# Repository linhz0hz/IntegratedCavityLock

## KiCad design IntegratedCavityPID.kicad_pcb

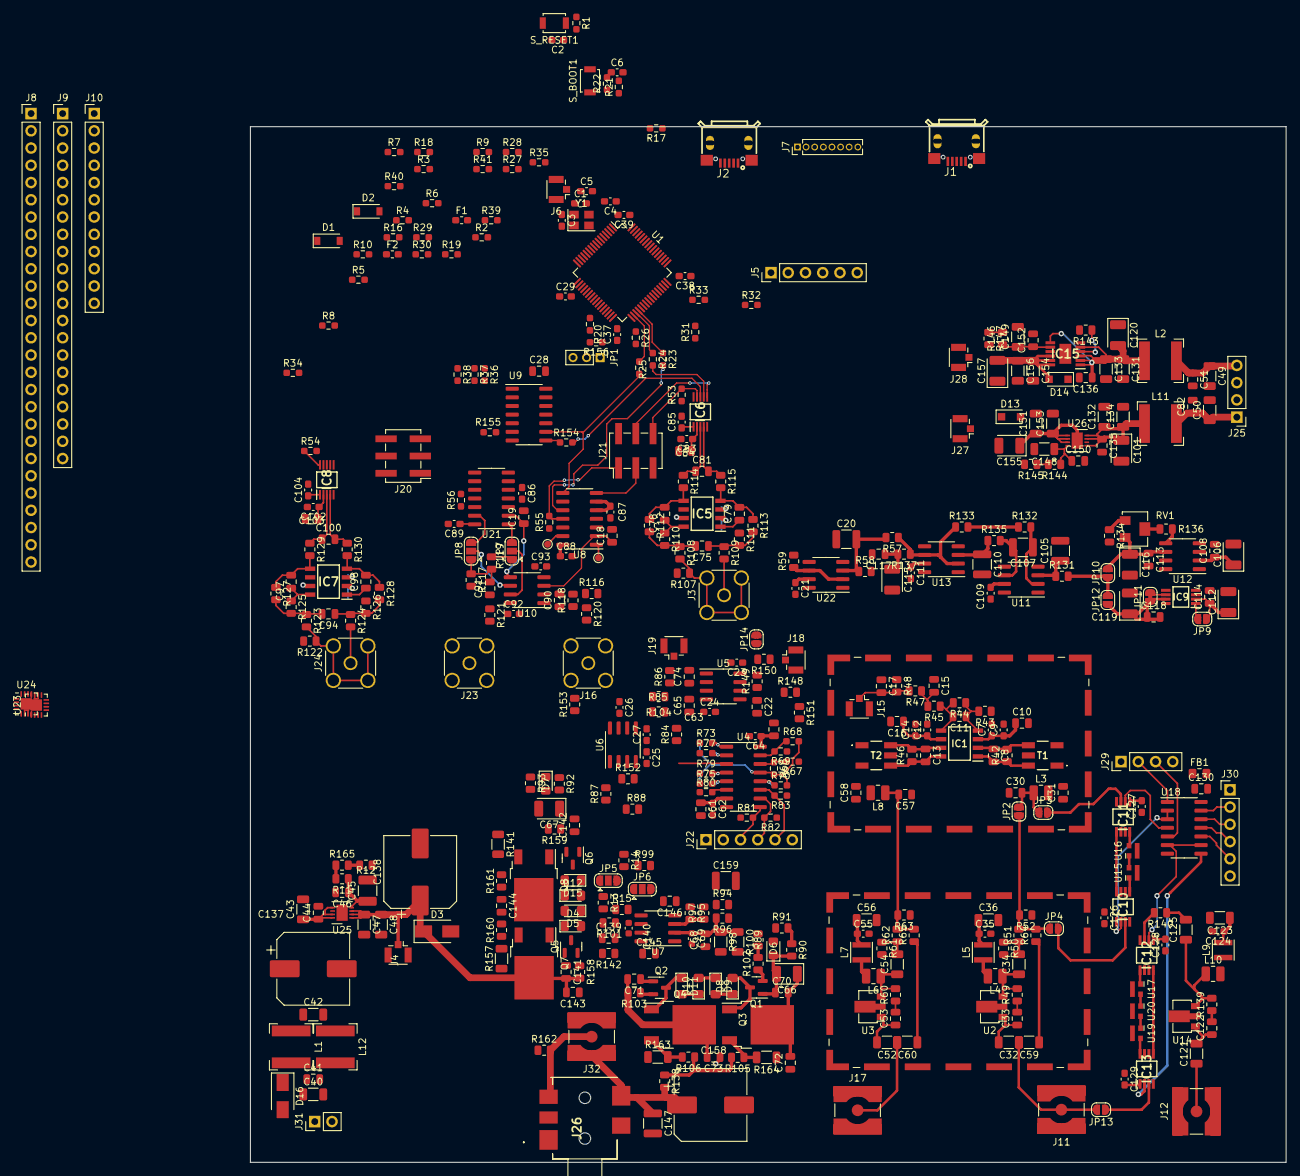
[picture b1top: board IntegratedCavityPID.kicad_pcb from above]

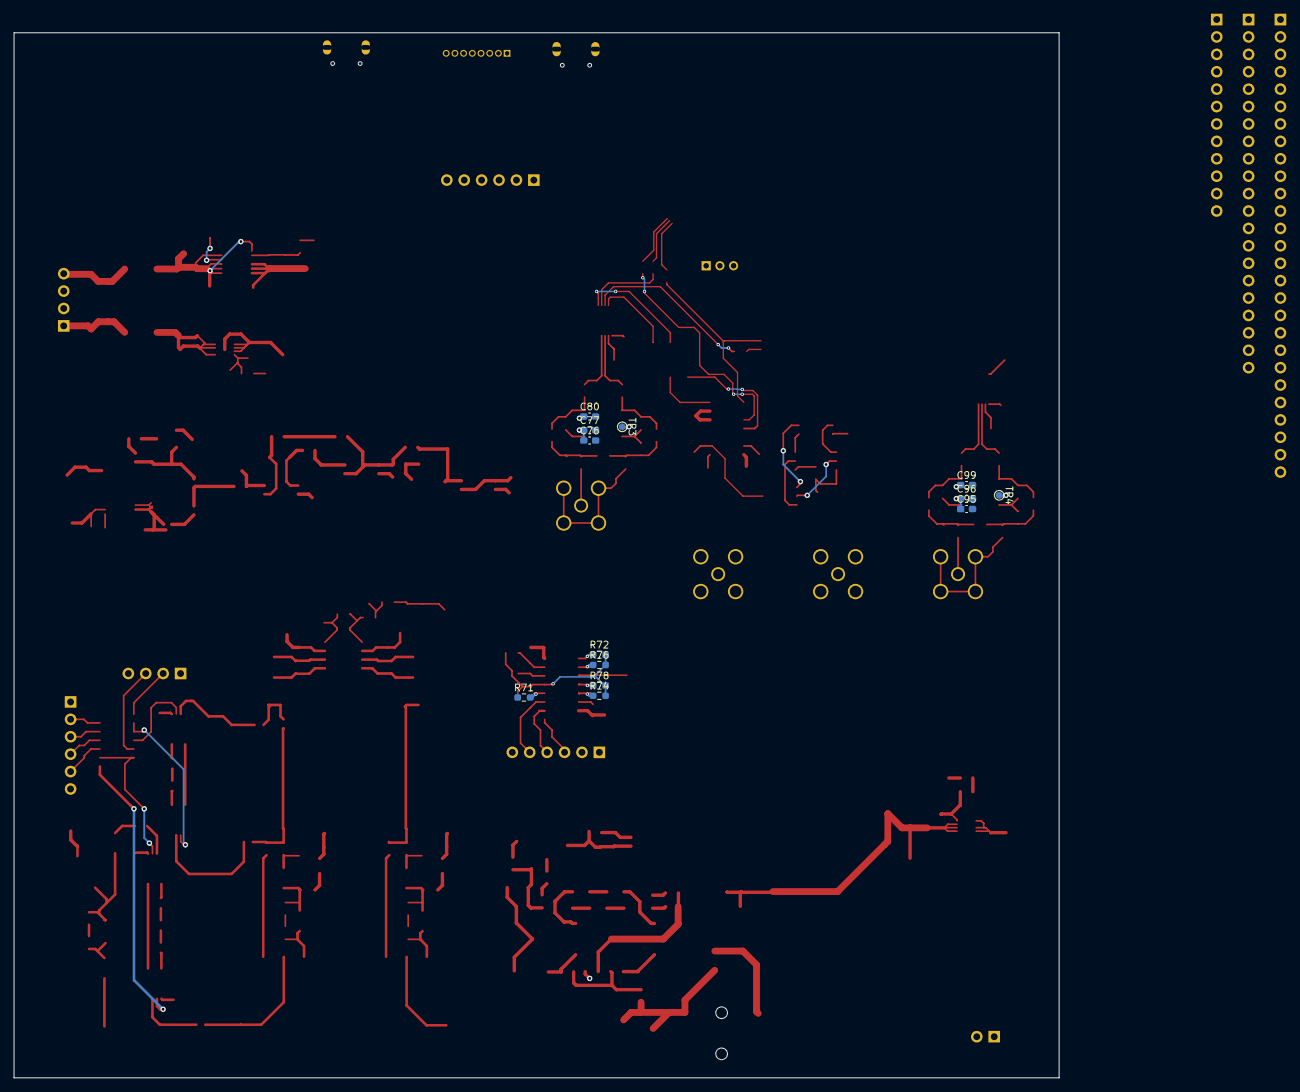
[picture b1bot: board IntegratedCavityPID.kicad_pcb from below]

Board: 4 copper layers, 152.5 x 152.5 mm, 456 parts (13 on the bottom side), 306 nets.

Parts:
C1, C3, C4, C5: 10p; C_0603_1608Metric_Pad1.08x0.95mm_HandSolder
C2, C6, C29, C37, C38, C39: X7R 0.1u; C_0603_1608Metric_Pad1.08x0.95mm_HandSolder
C7, C12: 10n; C_0603_1608Metric_Pad1.08x0.95mm_HandSolder
C8, C13: 22p; C_0805_2012Metric
C9, C14, C21, C23, C24, C25, C26, C27, C62, C64, C80, C83, C85, C86, C87, C88, C89, C92, C93, C99, C102, C104, C109, C111, C126, C127, C128, C129: 0.1uF; C_0603_1608Metric_Pad1.08x0.95mm_HandSolder
C10, C16, C61, C63, C84, C103: 1uF; C_0805_2012Metric
C11: 100p; C_0805_2012Metric
C15, C17: 4.7n; C_0805_2012Metric
C18, C19, C22, C65, C74, C117: dnp; C_0805_2012Metric
C20, C105, C107, C110, C147, C159: ECPU1C105MA5; C_1210_3225Metric
C28, C41, C44, C46, C51, C70, C71, C72, C73, C82, C130, C135, C136, C141, C142, C143, C144, C145, C146, C150, C152: 0.1uF; C_0805_2012Metric
C30, C31, C57, C58: 150p; C_0805_2012Metric
C32, C34, C36, C52, C54, C56, C59, C60, C121, C123, C125: 1u; C_1206_3216Metric
C33, C53, C108, C113, C114, C118, C122: 0.1u; C_0805_2012Metric
C35, C55, C124: 0.1u; C_0603_1608Metric_Pad1.08x0.95mm_HandSolder
C40, C42, C48: 2.2uF; C_1206_3216Metric
C43, C47, C133, C134, C151, C154: 1uF; C_1206_3216Metric
C45: dnp; C_1210_3225Metric_Pad1.33x2.70mm_HandSolder
C49, C50, C131, C132, C153, C156: 4.7uF; C_1206_3216Metric
C66, C67, C115: TAJA106K016RNJ; CP_EIA-3528-12_Kemet-T
C68, C139: dnp 100p; C_0805_2012Metric
C69, C140: 22p; C_0603_1608Metric
C75, C94: 2.2nF C0G; C_0805_2012Metric
C76, C77, C95, C96: dnp; C_0603_1608Metric_Pad1.08x0.95mm_HandSolder
C78, C79, C97, C98: 1nF C0G; C_0805_2012Metric
C81, C100: 10nF C0G; C_0805_2012Metric
C90, C91: 100pF; C_0805_2012Metric
C101, C120, C155, C157: tant 10uF; CP_EIA-3528-15_AVX-H
C106, C112, C116, C119: C_Polarized; CP_EIA-3528-12_Kemet-T
C137, C138, C158: OVK151M1VTR-1013; CP_Elec_10x10.5
C148, C149: dnp; C_1206_3216Metric
D1, D2: B5819W; D_SOD-123
D3, D16: SS210; D_SMA
D4, D5, D8, D9, D10, D11, D12, D15: 1N4148W; D_SOD-323_HugePad
D6, D7: NCD0805R1; LED_0805_2012Metric_Pad1.15x1.40mm_HandSolder
D13, D14: B5819W SL; D_SOD-123F
F1, F2: 0467.375NRHF; Fuse_0603_1608Metric_Pad1.05x0.95mm_HandSolder
FB1: GZ2012D601TF; L_0805_2012Metric_Pad1.15x1.40mm_HandSolder
IC1: AD835ARZ; SOIC127P600X175-8N
IC5, IC7: THS4521IDR; SOIC127P600X175-8N
IC6, IC8: ADS8863IDGS; SOP50P490X110-10N
IC9: LTC6655BHMS8-4.096#PBF; SOP65P490X110-8N
IC10, IC11, IC12, IC13: PE4250MLI-Z; SOP65P488X107-8N
IC15: LT3090EMSE#PBF; SOP65P490X110-13N
J1, J2: U254-051T-4BH83-S1S; MICRO-USB-SMD_U254-051T-4BH83-S1S
J3, J16, J23, J24: Conn_Coaxial; SMA_Amphenol_132134_Vertical
J4, J27, J28: Conn_Coaxial; U.FL_Hirose_U.FL-R-SMT-1_Vertical
J5: debug; PinHeader_1x06_P2.54mm_Vertical
J6: Clock_in; U.FL_Hirose_U.FL-R-SMT-1_Vertical
J7: Conn_01x08; PinHeader_1x08_P1.27mm_Vertical
J8: Conn_01x30_Male; PinHeader_1x27_P2.54mm_Vertical
J9: Conn_01x21_Male; PinHeader_1x21_P2.54mm_Vertical
J10: Conn_01x12_Male; PinHeader_1x12_P2.54mm_Vertical
J11, J12, J17, J32: SMA; SMA_Amphenol_132134-10_Vertical
J13, J14: RFShield_OnePiece; 21187222_RF_shield
J15, J18, J19: u.fl; U.FL_Hirose_U.FL-R-SMT-1_Vertical
J20, J21: B-2100N06P-B111; PinHeader_2x03_P2.54mm_Vertical_SMD
J22: mux; PinHeader_1x06_P2.54mm_Vertical
J25, J29: Conn_01x04; PinHeader_1x04_P2.54mm_Vertical
J26: SJ1-3514-SMT-TR; SJ13514SMTTR
J30: Conn_01x06; PinHeader_1x06_P2.54mm_Vertical
J31: Conn_01x02; PinHeader_1x02_P2.54mm_Vertical
JP1: Jumper_3_Open; PinHeader_1x03_P2.00mm_Vertical
JP2, JP3, JP4, JP9, JP10, JP12, JP13, JP14: sjp; SolderJumper-2_P1.3mm_Open_RoundedPad1.0x1.5mm
JP5, JP6, JP7, JP8: sjp; SolderJumper-3_P1.3mm_Open_RoundedPad1.0x1.5mm
JP11: sjp; SolderJumper-2_P1.3mm_Bridged_RoundedPad1.0x1.5mm
L1, L2, L11, L12: SWPA6028S180MT; L_Bourns-SRN6028
L3, L8: FHW0805UCR47JGT; L_1008_2520Metric
L4, L6, L10: FHW1008UCR47JGT; L_1008_2520Metric
L5, L7, L9: SWPA3012S4R7MT; L_Taiyo-Yuden_MD-3030
Q1, Q5: MMBT3906; SOT-23
Q2, Q6: mmbt3904; SOT-23
Q3, Q7: 2SCR573; TO-252-2
Q4, Q8: 2SAR573; TO-252-2
R1, R20, R21, R22, R81, R82, R83: 10k; R_0603_1608Metric_Pad0.98x0.95mm_HandSolder
R2, R3, R4, R5, R6, R7, R8, R9, R10, R23, R24, R25, R26, R27, R28, R29, R30, R31, R32, R33, R34, R35, R36, R37, R38, R39, R40, R41, R53, R54, R55, R56, R154, R155, R156: 27; R_0603_1608Metric_Pad0.98x0.95mm_HandSolder
R11: 0805W8F2204T5E; R_0805_2012Metric
R12, R51, R62, R84, R87, R107, R122, R137, R140, R148, R151, R152, R153: 0; R_0805_2012Metric
R13, R94: 33; R_0805_2012Metric
R14, R15, R95, R96: 270; R_0805_2012Metric
R16, R17, R18, R19: 4k7; R_0603_1608Metric_Pad0.98x0.95mm_HandSolder
R42, R46: 220; R_0805_2012Metric
R43, R47, R59, R97, R99, R118, R119: 100; R_0805_2012Metric
R44: 470; R_0805_2012Metric
R45, R86, R149: 150; R_0805_2012Metric
R48, R50, R52, R61, R63, R64, R65, R85, R88, R104, R116, R117: dnp; R_0805_2012Metric
R49, R60, R139: 1.5k; R_0805_2012Metric
R57, R58, R132, R133, R134, R136: 10k; R_0805_2012Metric
R66: 560; R_0603_1608Metric_Pad0.98x0.95mm_HandSolder
R67, R80: 220; R_0603_1608Metric_Pad0.98x0.95mm_HandSolder
R68, R70: 1.5k; R_0603_1608Metric_Pad0.98x0.95mm_HandSolder
R69: 150; R_0603_1608Metric_Pad0.98x0.95mm_HandSolder
R71, R73, R75, R77, R79: 47; R_0603_1608Metric_Pad0.98x0.95mm_HandSolder
R72, R74, R76, R78: dnp; R_0603_1608Metric_Pad0.98x0.95mm_HandSolder
R89, R93, R138, R162: 0R; R_0805_2012Metric
R90, R91, R92: PTFR0805B3K30N9; R_0805_2012Metric
R98, R100: 1k8; R_1206_3216Metric
R101, R142: 1k8; R_0805_2012Metric
R102, R103, R158, R159: PTFR0805B390RN9; R_0805_2012Metric
R105, R106, R114, R115, R120, R121, R129, R130, R160, R161: 10; R_0805_2012Metric
R108, R109, R123, R124: 560; R_0805_2012Metric
R110, R111, R125, R126: 390; R_0805_2012Metric
R112, R113, R127, R128, R131, R135, R147: 1k; R_0805_2012Metric
R141, R157, R163, R164: 2k2; R_1206_3216Metric
R143: 15k; R_0805_2012Metric
R144: 470k; R_0805_2012Metric
R145: 56k; R_0805_2012Metric
R146: 100k; R_0805_2012Metric
R150: 330; R_0805_2012Metric
R165: 0805W8F1004T5E; R_0805_2012Metric
RV1: dnp; Potentiometer_Bourns_3224W_Vertical
S_BOOT1: GT-TC032A-H015-L1; SW_SPST_B3U-1000P
S_RESET1: GT-TC032A-H015-L1; SW_SPST_B3U-1000P
T1, T2: MABA-007532-CF18A0; MABA007532CF18A0
TP1, TP2, TP3, TP4: tp; TestPoint_Pad_D1.0mm
U1: CH32V307RCT6; LQFP-64_10x10mm_P0.5mm
U2, U3, U14: PHA-13LN; SOT-89-3
U4: 74HC4051M/TR; SOIC-16_3.9x9.9mm_P1.27mm
U5, U7: ADA4075-2; SOIC-8_3.9x4.9mm_P1.27mm
U6: ADG419BR; SOIC-8_3.9x4.9mm_P1.27mm
U8, U21: MAX5719xSD; SOIC-14_3.9x8.7mm_P1.27mm
U9, U18: 74HC04; SOIC-14_3.9x8.7mm_P1.27mm
U10: ADA4841-2; SOIC-8_3.9x4.9mm_P1.27mm
U11, U22: OPA388; SOIC-8_3.9x4.9mm_P1.27mm
U12: ADR421ARZ; SOIC-8_3.9x4.9mm_P1.27mm
U13: THS4281; SOIC-8_3.9x4.9mm_P1.27mm
U15, U16: PAT1220-C-6DB; RF_Attenuator_Susumu_PAT1220
U17, U19, U20: PAT1220-C-8DB; RF_Attenuator_Susumu_PAT1220
U23, U24: THS4551xRGT; VQFN-16-1EP_3x3mm_P0.5mm_EP1.68x1.68mm
U25, U26: LT3080xDD; DFN-8-1EP_3x3mm_P0.5mm_EP1.66x2.38mm
Y1: X32258MOB4SI; Crystal_SMD_SeikoEpson_TSX3225-4Pin_3.2x2.5mm

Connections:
+3.3V: C28.2, IC6.10 (DVDD), IC8.10 (DVDD), R53.1, R54.1, U9.14 (VCC)
+3.3VA: C83.1, C84.1, C102.1, C103.1, IC6.2 (AVDD), IC8.2 (AVDD)
+3V3: C29.2, C37.2, C38.2, C39.2, J5.1, J7.4, J8.1, J8.15, J8.19, J8.26, J9.1, J9.8, J9.15, J10.4, JP1.3 (B), R1.2, R16.2, R17.2, R18.2, R19.2, S_BOOT1.2 (B), U1.1 (VBAT), U1.13 (VDDA), U1.19 (VDD), U1.32 (VDD), U1.48 (VDD), U1.64 (VDD)
+5VA: C12.1, C14.1, C16.1, C23.1, C25.2, C27.2, C35.1, C36.1, C55.1, C56.1, C63.1, C64.1, C80.1, C88.1, C89.1, C99.1, C106.1, C108.1, C109.1, C111.1, C112.1, C114.1, C123.1, C124.1, C126.2, C127.2, C128.2, C129.2, C151.1, C153.1, C155.1, D13.1 (K), FB1.1, IC1.6 (VP), IC5.3 (VS+), IC7.3 (VS+), IC9.2 (VIN), IC10.1 (V2), IC11.1 (V2), IC12.1 (V2), IC13.1 (V2), J27.1 (In), JP9.1 (A), L5.2, L7.2, L9.2, R104.1, U4.16 (VCC), U5.8 (V+), U6.4 (V+), U6.5 (VL), U8.14 (VDD), U11.7 (V+), U12.2 (VIN), U13.7 (V+), U21.14 (VDD), U26.1 (OUT), U26.2 (OUT), U26.3 (OUT), U26.9 (OUT)
+28V: C47.1, C48.1, C66.1, C70.2, C72.2, C138.1, C141.2, C143.2, C145.1, D3.1 (K), J4.1 (In), Q3.2 (C), Q7.2 (C), R89.2, R102.2, R158.2, U7.8 (V+), U25.1 (OUT), U25.2 (OUT), U25.3 (OUT), U25.9 (OUT)
-5VA: C7.1, C9.1, C10.1, C24.1, C26.2, C61.1, C62.1, C67.2, C71.2, C73.2, C142.2, C144.2, C146.1, C154.1, C156.1, C157.2, D14.2 (A), IC1.3 (VN), IC15.10 (OUT_1), IC15.11 (OUT_2), IC15.12 (OUT_3), J28.1 (In), Q4.2 (C), Q8.2 (C), R93.2, R103.2, R159.2, U4.7 (VEE), U5.4 (V-), U6.7 (V-), U7.4 (V-)
/main/AmplifiedMultiplier/Attn_In_A: IC10.3 (RFC), JP4.2 (B)
/main/AmplifiedMultiplier/Attn_Out_A: IC11.3 (RFC), JP3.2 (B)
/main/AmplifiedMultiplier/Attn_Out_B: IC13.3 (RFC), JP13.1 (A)
/main/AmplifiedMultiplier/HF_attn_mux/A_ctrl_n: IC11.2 (V1), U18.4
/main/AmplifiedMultiplier/HF_attn_mux/A_ctrl_p: IC10.2 (V1), U18.2, U18.3
/main/AmplifiedMultiplier/HF_attn_mux/B_ctrl_n: IC13.2 (V1), U18.8
/main/AmplifiedMultiplier/HF_attn_mux/B_ctrl_p: IC12.2 (V1), U18.6, U18.9
/main/AmplifiedMultiplier/HF_attn_mux/IN_B: C121.1, J12.1 (In)
/main/AmplifiedMultiplier/LC_bandpass1/in: C57.2, L8.1, R62.2, R63.2, R65.2
/main/AmplifiedMultiplier/LC_bandpass1/out: C58.2, L8.2, T2.3 (PRIMARY)
/main/AmplifiedMultiplier/LC_bandpass/in: C30.2, JP2.2 (B), JP3.1 (A), L3.1
/main/AmplifiedMultiplier/LC_bandpass/out: C31.2, L3.2, T1.1 (PRIMARY_DOT)
/main/AmplifiedMultiplier/Preamp_mixer1/in: C52.1, C60.2, J17.1 (In)
/main/AmplifiedMultiplier/Preamp_mixer/in: C32.1, C59.2, J11.1 (In), JP13.2 (B)
/main/AmplifiedMultiplier/Preamp_mixer/out: JP2.1 (A), JP4.1 (A), R51.2, R52.2, R64.2
/main/AnalogLoop/Attenuation_Select/A1: R66.1, R67.2, U4.14 (A1)
/main/AnalogLoop/Attenuation_Select/A2: R68.1, R69.2, U4.15 (A2)
/main/AnalogLoop/Attenuation_Select/A3: R70.1, R71.2, U4.12 (A3)
/main/AnalogLoop/Attenuation_Select/A4: R72.1, R73.2, U4.1 (A4)
/main/AnalogLoop/Attenuation_Select/A5: R74.1, R75.2, U4.5 (A5)
/main/AnalogLoop/Attenuation_Select/A6: R76.1, R77.2, U4.2 (A6)
/main/AnalogLoop/Attenuation_Select/A7: R78.1, R79.2, U4.4 (A7)
/main/AnalogLoop/Attenuation_Select/input: R66.2, R68.2, R70.2, R72.2, R74.2, R76.2, R78.2, R151.2, U4.13 (A0)
/main/AnalogLoop/Attenuation_Select/to_opamp: R84.1, U4.3 (A)
/main/AnalogLoop/Piezo_Drive/bias_h: C66.2, C70.1, C141.1, D6.1 (K), Q1.1 (B), Q5.1 (B), R90.2
/main/AnalogLoop/Piezo_Drive/bias_l: C71.1, C142.1, Q2.1 (B), Q6.1 (B)
/main/AnalogLoop/Piezo_Drive/input: R14.1, R87.1, R88.1, R95.1
/main/AnalogLoop/Piezo_Drive/offset: R97.2, R99.2, R153.1
/main/AnalogLoop/Piezo_Drive/out_A_n: Q4.3 (E), R106.2, R163.2
/main/AnalogLoop/Piezo_Drive/out_A_p: Q3.3 (E), R105.1, R164.2
/main/AnalogLoop/Piezo_Drive/out_B_n: Q8.3 (E), R141.2, R161.2
/main/AnalogLoop/Piezo_Drive/out_B_p: Q7.3 (E), R157.2, R160.1
/main/AnalogLoop/Piezo_Drive/piezo_fast: J26.3 (RING), J32.1 (In), R162.2
/main/AnalogLoop/Piezo_Drive/piezo_slow: C147.1, C158.1, J26.2 (TIP), J32.2 (Ext), R138.2
/main/DataConverters/ADC_buffered_1/AINN: C81.2, IC6.4 (AINN), R115.1
/main/DataConverters/ADC_buffered_1/AINP: C81.1, IC6.3 (AINP), R114.1
/main/DataConverters/ADC_buffered_1/In_neg: J3.2 (Ext), R107.1, R108.2
/main/DataConverters/ADC_buffered_1/In_pos: J3.1 (In), JP14.2 (B), R109.2
/main/DataConverters/ADC_buffered_1/PDn: IC5.7 (~PD), TP3.1
/main/DataConverters/ADC_buffered_2/AINN: C100.2, IC8.4 (AINN), R130.1
/main/DataConverters/ADC_buffered_2/AINP: C100.1, IC8.3 (AINP), R129.1
/main/DataConverters/ADC_buffered_2/In_neg: J24.2 (Ext), R122.1, R123.2
/main/DataConverters/ADC_buffered_2/In_pos: J24.1 (In), R124.2
/main/DataConverters/ADC_buffered_2/PDn: IC7.7 (~PD), TP4.1
/main/DataConverters/DAC_buffered/DAC_Ref: C86.1, C87.1, U8.5 (REFS), U8.6 (REFF), U21.5 (REFS), U21.6 (REFF)
/main/microcontroller/BOOT0: R21.1, U1.60 (BOOT0)
/main/microcontroller/BOOT1: R20.1, U1.28 (PB2)
/main/microcontroller/NRST: C2.1, R1.1, S_RESET1.1 (A), U1.7 (NRST)
/main/microcontroller/PA0: R9.1, U1.14 (PA0)
/main/microcontroller/PA1: R10.1, U1.15 (PA1)
/main/microcontroller/PA2: R41.1, U1.16 (PA2)
/main/microcontroller/PA3: R40.1, U1.17 (PA3)
/main/microcontroller/PA8: R33.1, U1.41 (PA8)
/main/microcontroller/PA9: R32.1, U1.42 (PA9)
/main/microcontroller/PA10: R31.1, U1.43 (PA10)
/main/microcontroller/PB0: R30.1, U1.26 (PB0)
/main/microcontroller/PB1: R29.1, U1.27 (PB1)
/main/microcontroller/PB8_I2C1_SCL: R2.1, R16.1, U1.61 (PB8)
/main/microcontroller/PB9_I2C1_SDA: R3.1, R17.1, U1.62 (PB9)
/main/microcontroller/PB10_I2C2_SCL: R19.1, R28.1, U1.29 (PB10)
/main/microcontroller/PB11_I2C2_SDA: R18.1, R27.1, U1.30 (PB11)
/main/microcontroller/PC0: J8.8, U1.8 (PC0)
/main/microcontroller/PC1: J8.9, U1.9 (PC1)
/main/microcontroller/PC2: J8.21, U1.10 (PC2)
/main/microcontroller/PC3: R8.1, U1.11 (PC3)
/main/microcontroller/PC4: J10.3, U1.24 (PC4)
/main/microcontroller/PC5: J10.2, U1.25 (PC5)
/main/microcontroller/PC6_I2S2MCK: R35.1, U1.37 (PC6)
/main/microcontroller/PC7_I2S3MCK: R34.1, U1.38 (PC7)
/main/microcontroller/PC13_TPR_RTC: J8.11, U1.2 (PC13)
/main/microcontroller/PC14_OSC32_I: C4.2, J8.12, U1.3 (PC14)
/main/microcontroller/PC15_OSC32_O: C5.2, J8.13, U1.4 (PC15)
/main/microcontroller/SDIO_CK: J7.5, U1.53 (PC12)
/main/microcontroller/SDIO_CMD: J7.3, U1.54 (PD2)
/main/microcontroller/SDIO_D0: J7.7, U1.39 (PC8)
/main/microcontroller/SDIO_D1: J7.8, U1.40 (PC9)
/main/microcontroller/SDIO_D2: J7.1, U1.51 (PC10)
/main/microcontroller/SDIO_D3: J7.2, U1.52 (PC11)
/main/microcontroller/SPI1_CS: R39.1, U1.20 (PA4)
/main/microcontroller/SPI1_MISO: R37.1, U1.22 (PA6)
/main/microcontroller/SPI1_MOSI: R36.1, U1.23 (PA7)
/main/microcontroller/SPI1_SCK: R38.1, U1.21 (PA5)
/main/microcontroller/SPI2_CS: R26.1, U1.33 (PB12)
/main/microcontroller/SPI2_MISO: R24.1, U1.35 (PB14)
/main/microcontroller/SPI2_MOSI: R23.1, U1.36 (PB15)
/main/microcontroller/SPI2_SCK: R25.1, U1.34 (PB13)
/main/microcontroller/SPI3_CS: R4.1, U1.50 (PA15)
/main/microcontroller/SPI3_MISO: R6.1, U1.56 (PB4)
/main/microcontroller/SPI3_MOSI: R7.1, U1.57 (PB5)
/main/microcontroller/SPI3_SCK: R5.1, U1.55 (PB3)
/main/microcontroller/SWCLK: J5.3, U1.49 (PA14)
/main/microcontroller/SWDIO: J5.4, U1.46 (PA13)
/main/microcontroller/USB_FS_DN: J1.2 (D-), U1.44 (PA11)
/main/microcontroller/USB_FS_DP: J1.3 (D+), U1.45 (PA12)
/main/microcontroller/USB_HS_DN: J2.2 (D-), U1.58 (PB6)
/main/microcontroller/USB_HS_DP: J2.3 (D+), U1.59 (PB7)
/main/microcontroller/Vin: D1.1 (K), D2.1 (K), J5.5, J5.6
/main/microcontroller/XI: C1.2, J6.1 (In), U1.5 (OSC_IN), Y1.3
/main/microcontroller/XO: C3.2, U1.6 (OSC_OUT), Y1.1
ADC1_CONV: IC6.6 (CONVST), J21.4
ADC1_DIN: IC6.9 (DIN), J21.6, R53.2
ADC1_DOUT: IC6.7 (DOUT), R24.2
ADC1_SCK: IC6.8 (SCLK), R154.2
ADC2_CONV: IC8.6 (CONVST), J20.4
ADC2_DIN: IC8.9 (DIN), J20.6, R54.2
ADC2_DOUT: IC8.7 (DOUT), R37.2
ADC2_SCK: IC8.8 (SCLK), R155.2
DAC1_CS: J21.3, U8.7 (~CS)
DAC1_DIN: R23.2, U8.10 (DIN)
DAC1_LDAC: J21.1, R55.2, U8.11 (~LDAC)
DAC1_SCLK: R25.2, U8.8 (SCLK), U9.9
DAC1_output: J16.1 (In), R120.2, R153.2
DAC2_CS: J20.3, U21.7 (~CS)
DAC2_DIN: R36.2, U21.10 (DIN)
DAC2_LDAC: J20.1, R56.2, U21.11 (~LDAC)
DAC2_SCLK: R38.2, U9.5, U21.8 (SCLK)
Error_Buffered: JP14.1 (A), R149.2, R150.2, U5.7
GND: C1.1, C2.2, C3.1, C4.1, C5.1, C6.1, C7.2, C9.2, C10.2, C12.2, C14.2, C15.1, C16.2, C17.1, C18.2, C19.2, C20.1, C21.2, C22.2, C23.2, C24.2, C25.1, C26.1, C27.1, C28.1, C29.1, C30.1, C31.1, C35.2, C36.2, C37.1, C38.1, C39.1, C42.2, C43.2, C44.2, C45.2, C46.2, C47.2, C48.2, C49.2, C50.2, C51.2, C55.2, C56.2, C57.1, C58.1, C61.2, C62.2, C63.2, C64.2, C65.1, C68.1, C72.1, C73.1, C76.2, C77.2, C80.2, C82.2, C83.2, C84.2, C85.2, C86.2, C87.2, C88.2, C89.2, C92.2, C93.1, C95.2, C96.2, C99.2, C101.2, C102.2, C103.2, C104.2, C105.2, C106.2, C108.2, C109.2, C110.2, C111.2, C112.2, C113.2, C114.2, C115.2, C116.2, C117.2, C118.2, C119.2, C120.1, C123.2, C124.2, C126.1, C127.1, C128.1, C129.1, C130.1, C131.2, C132.2, C133.2, C134.2, C135.2, C136.2, C137.2, C138.2, C139.1, C143.1, C144.1, C145.2, C146.2, C147.2, C148.2, C149.2, C150.2, C151.2, C152.2, C153.2, C154.2, C155.2, C156.2, C157.1, C158.2, C159.1, D3.2 (A), D13.2 (A), D14.1 (K), IC5.6 (VS-), IC6.5 (GND), IC7.6 (VS-), IC8.5 (GND), IC9.3 (GND_1), IC9.4 (GND_2), IC9.5 (GND_3), IC9.8 (GND_4), IC10.4 (N/C_OR_GND), IC10.6 (GND_1), IC10.7 (GND_2), IC11.4 (N/C_OR_GND), IC11.6 (GND_1), IC11.7 (GND_2), IC12.4 (N/C_OR_GND), IC12.6 (GND_1), IC12.7 (GND_2), IC13.4 (N/C_OR_GND), IC13.6 (GND_1), IC13.7 (GND_2), IC15.6 (IMONN), IC15.9 (GND), J1.5 (GND), J1.6 (Shield), J2.5 (GND), J2.6 (Shield), J4.2 (Ext), J5.2, J6.2 (Ext), J7.6, J8.2, J8.7, J8.10, J8.14, J8.16, J8.20, J8.23, J8.27, J9.5, J9.9, J9.11, J9.14, J9.18, J10.1, J10.8, J10.10, J11.2 (Ext), J12.2 (Ext), J13.1 (Shield), J14.1 (Shield), J15.2 (Ext), J16.2 (Ext), J17.2 (Ext), J18.2 (Ext), J19.2 (Ext), J20.2, J20.5, J21.2, J21.5, J22.1, J22.6, J23.2 (Ext), J25.2, J25.3, J26.1 (SLEEVE), J27.2 (Ext), J28.2 (Ext), J29.1, J29.4, J30.1, J30.6, JP1.1 (A), JP5.1 (A), JP6.3 (B), L12.2, R12.2, R22.2, R43.1, R48.1, R50.2, R52.1, R55.1, R56.1, R58.2, R61.2, R63.1, R67.1, R69.1, R71.1, R73.1, R75.1, R77.1, R79.1, R80.1, R81.1, R82.1, R83.1, R85.1, R88.2, R91.1, R92.1, R94.1, R107.2, R116.2, R117.2, R122.2, R134.2, R143.2, R145.2, R147.2, R152.2, R156.1, S_RESET1.2 (B), T1.3 (PRIMARY), T1.5 (SECONDARY_CENTRE_TAP), T2.1 (PRIMARY_DOT), T2.5 (SECONDARY_CENTRE_TAP), U1.12 (VSSA), U1.18 (VSS), U1.31 (VSS), U1.47 (VSS), U1.63 (VSS), U2.2 (GND), U3.2 (GND), U4.8 (GND), U6.3 (GND), U8.3 (AGNDF), U8.4 (AGNDS), U8.12 (DGND), U9.7 (GND), U11.4 (V-), U12.4 (GND), U13.4 (V-), U14.2 (GND), U15.3, U16.3, U17.3, U18.7 (GND), U19.3, U20.3, U21.3 (AGNDF), U21.4 (AGNDS), U21.12 (DGND), U22.4 (V-), Y1.2, Y1.4
Half_Ref: C76.1, C77.1, C95.1, C96.1, IC5.2 (VOCM), IC7.2 (VOCM), R59.2
Mixer_Demod: C17.2, J15.1 (In), R47.2, R48.2, R148.2, R151.1
unnamed: C6.2, R21.2, R22.1, S_BOOT1.1 (A)
unnamed: C8.1, IC1.2 (Y2), R42.2, T1.4 (SECONDARY)
unnamed: C8.2, IC1.1 (Y1), R42.1, T1.6 (SECONDARY_DOT)
unnamed: C11.1, IC1.4 (Z), R43.2, R44.1
unnamed: C11.2, IC1.5 (W), R44.2, R45.1
unnamed: C13.1, IC1.7 (X2), R46.2, T2.6 (SECONDARY_DOT)
unnamed: C13.2, IC1.8 (X1), R46.1, T2.4 (SECONDARY)
unnamed: C15.2, R45.2, R47.1
unnamed: C18.1, U8.2 (OUT), U10.3 (+)
unnamed: C19.1, U10.5 (+), U21.2 (OUT)
unnamed: C20.2, R57.2, R58.1, U22.3 (+)
unnamed: C21.1, U22.7 (V+)
unnamed: C22.1, R148.1, U5.5 (+)
unnamed: C32.2, C33.1, U2.1
unnamed: C33.2, R49.1
unnamed: C34.1, L4.1, R49.2, U2.3
unnamed: C34.2, R50.1, R51.1
unnamed: C40.1, C41.1, D16.1 (K), L1.1
unnamed: C40.2, C41.2, J31.2, L12.1
unnamed: C45.1, C46.1, R11.1, U25.4 (SET)
unnamed: C49.1, C51.1, J25.4, L2.1
unnamed: C50.1, C82.1, J25.1, L11.1
unnamed: C52.2, C53.1, U3.1
unnamed: C53.2, R60.1
unnamed: C54.1, L6.1, R60.2, U3.3
unnamed: C54.2, R61.1, R62.1
unnamed: C59.1, R64.1
unnamed: C60.1, R65.1
unnamed: C65.2, R84.2, U5.3 (+)
unnamed: C67.1, D7.2 (A), R92.2
unnamed: C68.2, C69.1, R96.2, R98.1, R100.1, U7.2 (-)
unnamed: C69.2, D9.1 (K), D10.2 (A), U7.1
unnamed: C74.1, R85.2, R86.1, R104.2, U5.2 (-)
unnamed: C74.2, J19.1 (In), R86.2, U5.1, U6.8
unnamed: C75.1, R109.1, R111.2, R113.2
unnamed: C75.2, R108.1, R110.2, R112.2
unnamed: C78.1, IC5.8 (VIN+), R110.1
unnamed: C78.2, IC5.5 (VOUT-), R112.1, R114.2
unnamed: C79.1, IC5.1 (V_IN-), R111.1
unnamed: C79.2, IC5.4 (VOUT+), R113.1, R115.2
unnamed: C90.1, R118.1, R120.1, U10.1
unnamed: C90.2, R116.1, R118.2, U10.2 (-)
unnamed: C91.1, JP7.2 (C), R121.1, U10.7
unnamed: C91.2, JP8.1 (A), R117.1, R119.2
unnamed: C94.1, R124.1, R126.2, R128.2
unnamed: C94.2, R123.1, R125.2, R127.2
unnamed: C97.1, IC7.8 (VIN+), R125.1
unnamed: C97.2, IC7.5 (VOUT-), R127.1, R129.2
unnamed: C98.1, IC7.1 (V_IN-), R126.1
unnamed: C98.2, IC7.4 (VOUT+), R128.1, R130.2
unnamed: C101.1, C132.1, C134.1, C135.1, L11.2, U26.5 (VCONTROL), U26.7 (IN), U26.8 (IN)
unnamed: C105.1, R131.1, U11.3 (+)
unnamed: C107.1, R132.2, U11.2 (-)
unnamed: C107.2, R135.2, U11.6
unnamed: C110.1, R135.1, U13.3 (+)
unnamed: C113.1, C116.1, JP10.1 (A), RV1.3, U12.6 (OUT)
unnamed: C115.1, C117.1, R137.2
unnamed: C118.1, C119.1, IC9.7 (VOUT_F), JP11.1 (A), JP12.1 (A)
unnamed: C121.2, C122.1, U14.1
unnamed: C122.2, R139.1
unnamed: C125.1, L10.1, R139.2, U14.3
unnamed: C125.2, R140.1
unnamed: C130.2, FB1.2, U18.14 (VCC)
unnamed: C42.1, C43.1, C44.1, C137.1, L1.2, U25.5 (VCONTROL), U25.7 (IN), U25.8 (IN)
unnamed: C139.2, C140.1, R15.2, R101.1, R142.1, U7.6 (-)
unnamed: C140.2, D5.1 (K), D12.2 (A), U7.7
unnamed: C148.1, C150.1, R144.1, U26.4 (SET)
unnamed: C149.1, C152.1, IC15.8 (SET), R146.1
unnamed: C159.2, R95.2, R97.1, U7.3 (+)
unnamed: D1.2 (A), F1.2
unnamed: D2.2 (A), F2.2
unnamed: D4.1 (K), D5.2 (A)
unnamed: D4.2 (A), Q5.3 (C), Q7.1 (B)
unnamed: D6.2 (A), R89.1
unnamed: D7.1 (K), R93.1
unnamed: D8.1 (K), D9.2 (A)
unnamed: D8.2 (A), Q1.3 (C), Q3.1 (B)
unnamed: D10.1 (K), D11.2 (A)
unnamed: D11.1 (K), Q2.3 (C), Q4.1 (B)
unnamed: D12.1 (K), D15.2 (A)
unnamed: D15.1 (K), Q6.3 (C), Q8.1 (B)
unnamed: F1.1, J2.1 (VBUS)
unnamed: F2.1, J1.1 (VBUS)
unnamed: IC9.1 (~SHDN), JP9.2 (B)
unnamed: IC9.6 (VOUT_S), JP11.2 (B)
unnamed: IC10.5 (RF1), U15.1
unnamed: IC10.8 (RF2), IC11.5 (RF1)
unnamed: IC11.8 (RF2), U16.2
unnamed: IC12.3 (RFC), R140.2
unnamed: IC12.5 (RF1), U17.1
unnamed: IC12.8 (RF2), IC13.5 (RF1)
unnamed: IC13.8 (RF2), U19.2
unnamed: C120.2, C131.1, C133.1, C136.1, IC15.1 (IN_1), IC15.2 (IN_2), IC15.3 (IN_3), IC15.5 (IMONP), IC15.7 (~SHDN), IC15.13 (EP_IN), L2.2
unnamed: IC15.4 (ILIM), R143.1
unnamed: J8.3, R4.2
unnamed: J8.4, R5.2
unnamed: J8.5, R6.2
unnamed: J8.6, R7.2
unnamed: J8.17, R2.2
unnamed: J8.18, R3.2
unnamed: J8.22, R8.2
unnamed: J8.24, R9.2
unnamed: J8.25, R10.2
unnamed: J9.2, R31.2
unnamed: J9.3, R32.2
unnamed: J9.4, R33.2
unnamed: J9.6, R34.2
unnamed: J9.7, R35.2
unnamed: J9.10, R26.2
unnamed: J9.12, R27.2
unnamed: J9.13, R28.2
unnamed: J9.16, R29.2
unnamed: J9.17, R30.2
unnamed: J10.9, R39.2
unnamed: J10.11, R40.2
unnamed: J10.12, R41.2
unnamed: J18.1 (In), R150.1
unnamed: J22.2, R80.2, U4.6 (~E)
unnamed: J22.3, R81.2, U4.9 (S2)
unnamed: J22.4, R82.2, U4.10 (S1)
unnamed: J22.5, R83.2, U4.11 (S0)
unnamed: J23.1 (In), R121.2
unnamed: J29.2, U18.1
unnamed: J29.3, U18.5
unnamed: J30.2, U18.13
unnamed: J30.3, U18.12
unnamed: J30.4, U18.11
unnamed: J30.5, U18.10
unnamed: D16.2 (A), J31.1
unnamed: JP1.2 (C), R20.2, R156.2
unnamed: JP5.2 (C), R13.1
unnamed: JP5.3 (B), JP6.1 (A), R14.2, R99.1
unnamed: JP6.2 (C), U7.5 (+)
unnamed: JP7.1 (A), R119.1
unnamed: JP7.3 (B), U21.1 (RFB)
unnamed: JP8.2 (C), U10.6 (-)
unnamed: JP8.3 (B), U21.13 (INV)
unnamed: L4.2, L5.1
unnamed: L6.2, L7.1
unnamed: L9.1, L10.2
unnamed: Q1.2 (E), R102.1
unnamed: Q2.2 (E), R103.1
unnamed: Q5.2 (E), R158.1
unnamed: Q6.2 (E), R159.1
unnamed: R11.2, R165.1
unnamed: R12.1, R165.2
unnamed: R13.2, R15.1
unnamed: R59.1, U22.2 (-), U22.6
unnamed: R87.2, U6.1
unnamed: R90.1, R91.2
unnamed: R94.2, R96.1
unnamed: R100.2, R164.1
unnamed: R101.2, R141.1
unnamed: R105.2, R106.1, R138.1
unnamed: R132.1, R133.2
unnamed: R134.1, RV1.1
unnamed: R136.1, U12.5 (TRIM)
unnamed: R136.2, RV1.2
unnamed: R142.2, R157.1
unnamed: R144.2, R145.1
unnamed: R146.2, R147.1
unnamed: R149.1, U5.6 (-)
unnamed: R152.1, U6.2
unnamed: R154.1, U9.8
unnamed: R155.1, U9.6
unnamed: R160.2, R161.1, R162.1
unnamed: R98.2, R163.1
unnamed: TP1.1, U8.13 (INV)
unnamed: TP2.1, U8.1 (RFB)
unnamed: U15.2, U16.1
unnamed: U17.2, U20.1
unnamed: U19.1, U20.2
unnamed: U23.5 (VS+), U23.6 (VS+), U23.7 (VS+), U23.8 (VS+)
unnamed: U23.13 (VS-), U23.14 (VS-), U23.15 (VS-), U23.16 (VS-)
unnamed: U24.5 (VS+), U24.6 (VS+), U24.7 (VS+), U24.8 (VS+)
unnamed: U24.13 (VS-), U24.14 (VS-), U24.15 (VS-), U24.16 (VS-)
Ref_Buf: C85.1, C104.1, IC6.1 (REF), IC8.1 (REF), R57.1, R133.1, R137.1, U13.2 (-), U13.6
VDD: C92.1, U10.8 (V+)
VSS: C93.2, U10.4 (V-)
Vref: JP10.2 (B), JP12.2 (B), R131.2

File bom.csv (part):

Designator,Footprint,Quantity,Value,LCSC Part #
J21,PinHeader_2x03_P2.54mm_Vertical_SMD,1,B-2100N06P-B111,
IC13,SOP65P488X107-8N,1,PE4250MLI-Z,
IC12,SOP65P488X107-8N,1,PE4250MLI-Z,
IC11,SOP65P488X107-8N,1,PE4250MLI-Z,
IC10,SOP65P488X107-8N,1,PE4250MLI-Z,
R156,R_0603_1608Metric_Pad0.98x0.95mm_HandSolder,1,27,
JP11,SolderJumper-2_P1.3mm_Bridged_RoundedPad1.0x1.5mm,1,sjp,
C28,C_0805_2012Metric,1,0.1uF,
J20,PinHeader_2x03_P2.54mm_Vertical_SMD,1,B-2100N06P-B111,
R155,R_0603_1608Metric_Pad0.98x0.95mm_HandSolder,1,27,
R154,R_0603_1608Metric_Pad0.98x0.95mm_HandSolder,1,27,
TP4,TestPoint_Pad_D1.0mm,1,tp,
TP3,TestPoint_Pad_D1.0mm,1,tp,
R153,R_0805_2012Metric,1,0,
TP2,TestPoint_Pad_D1.0mm,1,tp,
TP1,TestPoint_Pad_D1.0mm,1,tp,
C27,C_0603_1608Metric_Pad1.08x0.95mm_HandSolder,1,0.1uF,
R152,R_0805_2012Metric,1,0,
C26,C_0603_1608Metric_Pad1.08x0.95mm_HandSolder,1,0.1uF,
C25,C_0603_1608Metric_Pad1.08x0.95mm_HandSolder,1,0.1uF,
R151,R_0805_2012Metric,1,0,
JP14,SolderJumper-2_P1.3mm_Open_RoundedPad1.0x1.5mm,1,sjp,
R150,R_0805_2012Metric,1,330,
R149,R_0805_2012Metric,1,150,
R148,R_0805_2012Metric,1,0,
J19,U.FL_Hirose_U.FL-R-SMT-1_Vertical,1,u.fl,
J18,U.FL_Hirose_U.FL-R-SMT-1_Vertical,1,u.fl,
C24,C_0603_1608Metric_Pad1.08x0.95mm_HandSolder,1,0.1uF,
C23,C_0603_1608Metric_Pad1.08x0.95mm_HandSolder,1,0.1uF,
C22,C_0805_2012Metric,1,dnp,
U22,SOIC-8_3.9x4.9mm_P1.27mm,1,OPA388,
R59,R_0805_2012Metric,1,100,
R58,R_0805_2012Metric,1,10k,
R57,R_0805_2012Metric,1,10k,
C21,C_0603_1608Metric_Pad1.08x0.95mm_HandSolder,1,0.1uF,
C20,C_1210_3225Metric,1,ECPU1C105MA5,
C19,C_0805_2012Metric,1,dnp,
C18,C_0805_2012Metric,1,dnp,
U9,SOIC-14_3.9x8.7mm_P1.27mm,1,74HC04,
U21,SOIC-14_3.9x8.7mm_P1.27mm,1,MAX5719xSD,
R56,R_0603_1608Metric_Pad0.98x0.95mm_HandSolder,1,27,
R55,R_0603_1608Metric_Pad0.98x0.95mm_HandSolder,1,27,
R54,R_0603_1608Metric_Pad0.98x0.95mm_HandSolder,1,27,
R53,R_0603_1608Metric_Pad0.98x0.95mm_HandSolder,1,27,
Y1,Crystal_SMD_SeikoEpson_TSX3225-4Pin_3.2x2.5mm,1,X32258MOB4SI,
U13,SOIC-8_3.9x4.9mm_P1.27mm,1,THS4281,
U12,SOIC-8_3.9x4.9mm_P1.27mm,1,ADR421ARZ,
U11,SOIC-8_3.9x4.9mm_P1.27mm,1,OPA388,
U10,SOIC-8_3.9x4.9mm_P1.27mm,1,ADA4841-2,
U8,SOIC-14_3.9x8.7mm_P1.27mm,1,MAX5719xSD,
U1,LQFP-64_10x10mm_P0.5mm,1,CH32V307RCT6,
S_RESET1,SW_SPST_B3U-1000P,1,GT-TC032A-H015-L1,
S_BOOT1,SW_SPST_B3U-1000P,1,GT-TC032A-H015-L1,
RV1,Potentiometer_Bourns_3224W_Vertical,1,dnp,
R147,R_0805_2012Metric,1,1k,
R146,R_0805_2012Metric,1,100k,
R145,R_0805_2012Metric,1,33k,
R144,R_0805_2012Metric,1,470k,
R143,R_0805_2012Metric,1,15k,
R142,R_0805_2012Metric,1,33k,
R141,R_0805_2012Metric,1,470k,
R137,R_0805_2012Metric,1,0,
R136,R_0805_2012Metric,1,10k,
R135,R_0805_2012Metric,1,1k,
R134,R_0805_2012Metric,1,10k,
R133,R_0805_2012Metric,1,10k,
R132,R_0805_2012Metric,1,10k,
R131,R_0805_2012Metric,1,1k,
R130,R_0805_2012Metric,1,10,
R129,R_0805_2012Metric,1,10,
R128,R_0805_2012Metric,1,1k,
R127,R_0805_2012Metric,1,1k,
R126,R_0805_2012Metric,1,390,
R125,R_0805_2012Metric,1,390,
R124,R_0805_2012Metric,1,560,
R123,R_0805_2012Metric,1,560,
R122,R_0805_2012Metric,1,0,
R121,R_0805_2012Metric,1,10,
R120,R_0805_2012Metric,1,10,
R119,R_0805_2012Metric,1,100,
R118,R_0805_2012Metric,1,100,
R117,R_0805_2012Metric,1,dnp,
R116,R_0805_2012Metric,1,dnp,
R115,R_0805_2012Metric,1,10,
R114,R_0805_2012Metric,1,10,
R113,R_0805_2012Metric,1,1k,
R112,R_0805_2012Metric,1,1k,
R111,R_0805_2012Metric,1,390,
R110,R_0805_2012Metric,1,390,
R109,R_0805_2012Metric,1,560,
R108,R_0805_2012Metric,1,560,
R107,R_0805_2012Metric,1,0,
R41,R_0603_1608Metric_Pad0.98x0.95mm_HandSolder,1,27,
R40,R_0603_1608Metric_Pad0.98x0.95mm_HandSolder,1,27,
R39,R_0603_1608Metric_Pad0.98x0.95mm_HandSolder,1,27,
R38,R_0603_1608Metric_Pad0.98x0.95mm_HandSolder,1,27,
R37,R_0603_1608Metric_Pad0.98x0.95mm_HandSolder,1,27,
R36,R_0603_1608Metric_Pad0.98x0.95mm_HandSolder,1,27,
R35,R_0603_1608Metric_Pad0.98x0.95mm_HandSolder,1,27,
R34,R_0603_1608Metric_Pad0.98x0.95mm_HandSolder,1,27,
R33,R_0603_1608Metric_Pad0.98x0.95mm_HandSolder,1,27,
R32,R_0603_1608Metric_Pad0.98x0.95mm_HandSolder,1,27,
R31,R_0603_1608Metric_Pad0.98x0.95mm_HandSolder,1,27,
R30,R_0603_1608Metric_Pad0.98x0.95mm_HandSolder,1,27,
R29,R_0603_1608Metric_Pad0.98x0.95mm_HandSolder,1,27,
R28,R_0603_1608Metric_Pad0.98x0.95mm_HandSolder,1,27,
R27,R_0603_1608Metric_Pad0.98x0.95mm_HandSolder,1,27,
R26,R_0603_1608Metric_Pad0.98x0.95mm_HandSolder,1,27,
R25,R_0603_1608Metric_Pad0.98x0.95mm_HandSolder,1,27,
R24,R_0603_1608Metric_Pad0.98x0.95mm_HandSolder,1,27,
R23,R_0603_1608Metric_Pad0.98x0.95mm_HandSolder,1,27,
R22,R_0603_1608Metric_Pad0.98x0.95mm_HandSolder,1,10k,
R21,R_0603_1608Metric_Pad0.98x0.95mm_HandSolder,1,10k,
R20,R_0603_1608Metric_Pad0.98x0.95mm_HandSolder,1,10k,
R19,R_0603_1608Metric_Pad0.98x0.95mm_HandSolder,1,4k7,
R18,R_0603_1608Metric_Pad0.98x0.95mm_HandSolder,1,4k7,
R17,R_0603_1608Metric_Pad0.98x0.95mm_HandSolder,1,4k7,
R16,R_0603_1608Metric_Pad0.98x0.95mm_HandSolder,1,4k7,
R15,R_0603_1608Metric_Pad0.98x0.95mm_HandSolder,1,47k,
R14,R_0603_1608Metric_Pad0.98x0.95mm_HandSolder,1,47k,
R13,R_0603_1608Metric_Pad0.98x0.95mm_HandSolder,1,47k,
R12,R_0603_1608Metric_Pad0.98x0.95mm_HandSolder,1,47k,
R11,R_0603_1608Metric_Pad0.98x0.95mm_HandSolder,1,47k,
R10,R_0603_1608Metric_Pad0.98x0.95mm_HandSolder,1,27,
R9,R_0603_1608Metric_Pad0.98x0.95mm_HandSolder,1,27,
R8,R_0603_1608Metric_Pad0.98x0.95mm_HandSolder,1,27,
R7,R_0603_1608Metric_Pad0.98x0.95mm_HandSolder,1,27,
R6,R_0603_1608Metric_Pad0.98x0.95mm_HandSolder,1,27,
R5,R_0603_1608Metric_Pad0.98x0.95mm_HandSolder,1,27,
R4,R_0603_1608Metric_Pad0.98x0.95mm_HandSolder,1,27,
R3,R_0603_1608Metric_Pad0.98x0.95mm_HandSolder,1,27,
R2,R_0603_1608Metric_Pad0.98x0.95mm_HandSolder,1,27,
R1,R_0603_1608Metric_Pad0.98x0.95mm_HandSolder,1,10k,
L12,L_Taiyo-Yuden_MD-3030,1,SWPA3012S100MT,
L11,L_Taiyo-Yuden_MD-3030,1,SWPA3012S100MT,
JP12,SolderJumper-2_P1.3mm_Open_RoundedPad1.0x1.5mm,1,sjp,
JP10,SolderJumper-2_P1.3mm_Open_RoundedPad1.0x1.5mm,1,sjp,
JP9,SolderJumper-2_P1.3mm_Open_RoundedPad1.0x1.5mm,1,sjp,
JP8,SolderJumper-3_P1.3mm_Open_RoundedPad1.0x1.5mm,1,sjp,
JP7,SolderJumper-3_P1.3mm_Open_RoundedPad1.0x1.5mm,1,sjp,
JP1,PinHeader_1x03_P2.00mm_Vertical,1,Jumper_3_Open,
J28,U.FL_Hirose_U.FL-R-SMT-1_Vertical,1,Conn_Coaxial,
J27,U.FL_Hirose_U.FL-R-SMT-1_Vertical,1,Conn_Coaxial,
J26,U.FL_Hirose_U.FL-R-SMT-1_Vertical,1,Conn_Coaxial,
J25,PinHeader_1x04_P2.54mm_Vertical,1,Conn_01x04,
J24,SMA_Amphenol_132134_Vertical,1,Conn_Coaxial,
J23,SMA_Amphenol_132134_Vertical,1,Conn_Coaxial,
J16,SMA_Amphenol_132134_Vertical,1,Conn_Coaxial,
J7,PinHeader_1x08_P1.27mm_Vertical,1,Conn_01x08,
J6,U.FL_Hirose_U.FL-R-SMT-1_Vertical,1,Clock_in,
J5,PinHeader_1x06_P2.54mm_Vertical,1,debug,
J3,SMA_Amphenol_132134_Vertical,1,Conn_Coaxial,
J2,MICRO-USB-SMD_U254-051T-4BH83-S1S,1,U254-051T-4BH83-S1S,
J1,MICRO-USB-SMD_U254-051T-4BH83-S1S,1,U254-051T-4BH83-S1S,
IC16,SOP65P490X110-9N,1,LT3085EMS8E#TRPBF,
IC15,SOP65P490X110-13N,1,LT3090EMSE#PBF,
IC14,SOP65P490X110-9N,1,LT3085EMS8E#TRPBF,
IC9,SOP65P490X110-8N,1,LTC6655BHMS8-4.096#PBF,
IC8,SOP50P490X110-10N,1,ADS8863IDGS,
IC7,SOIC127P600X175-8N,1,THS4521IDR,
IC6,SOP50P490X110-10N,1,ADS8863IDGS,
IC5,SOIC127P600X175-8N,1,THS4521IDR,
F2,Fuse_0603_1608Metric_Pad1.05x0.95mm_HandSolder,1,0467.375NRHF,
F1,Fuse_0603_1608Metric_Pad1.05x0.95mm_HandSolder,1,0467.375NRHF,
D14,D_SOD-123F,1,B5819W SL,
D13,D_SOD-123F,1,B5819W SL,
D12,D_SOD-123F,1,B5819W SL,
D2,D_SOD-123,1,B5819W,
D1,D_SOD-123,1,B5819W,
C157,CP_EIA-3528-15_AVX-H,1,tant 10uF,
C156,C_1206_3216Metric,1,4.7uF,
C155,CP_EIA-3528-15_AVX-H,1,tant 10uF,
C154,C_1206_3216Metric,1,1uF,
C153,C_1206_3216Metric,1,4.7uF,
C152,C_0805_2012Metric,1,0.1uF,
C151,C_1206_3216Metric,1,1uF,
C150,C_0805_2012Metric,1,0.1uF,
C149,C_1206_3216Metric,1,dnp,
C148,C_1206_3216Metric,1,dnp,
C147,CP_EIA-3528-15_AVX-H,1,tant 10uF,
C146,C_1206_3216Metric,1,4.7uF,
C145,C_1206_3216Metric,1,1uF,
C144,C_0805_2012Metric,1,0.1uF,
C143,C_1206_3216Metric,1,dnp,
C142,C_0805_2012Metric,1,0.1uF,
C141,C_0805_2012Metric,1,0.1uF,
C140,C_1206_3216Metric,1,1uF,
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
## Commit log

2023-02-07 Preliminery commit
2023-02-07 Preliminary layout of analog portions
2023-02-08 Analog section complete!
2023-02-08 Digital section half finished
2023-02-09 First finished draft
2023-02-09 Moved 3.3VA supply out of the ADC area, to have that area cleaner
2023-02-09 First finished version. Still need to check some footprint for critical parts and also refine the part numbers before order
2023-02-10 Version 1.0 submitted to JLCPCB
